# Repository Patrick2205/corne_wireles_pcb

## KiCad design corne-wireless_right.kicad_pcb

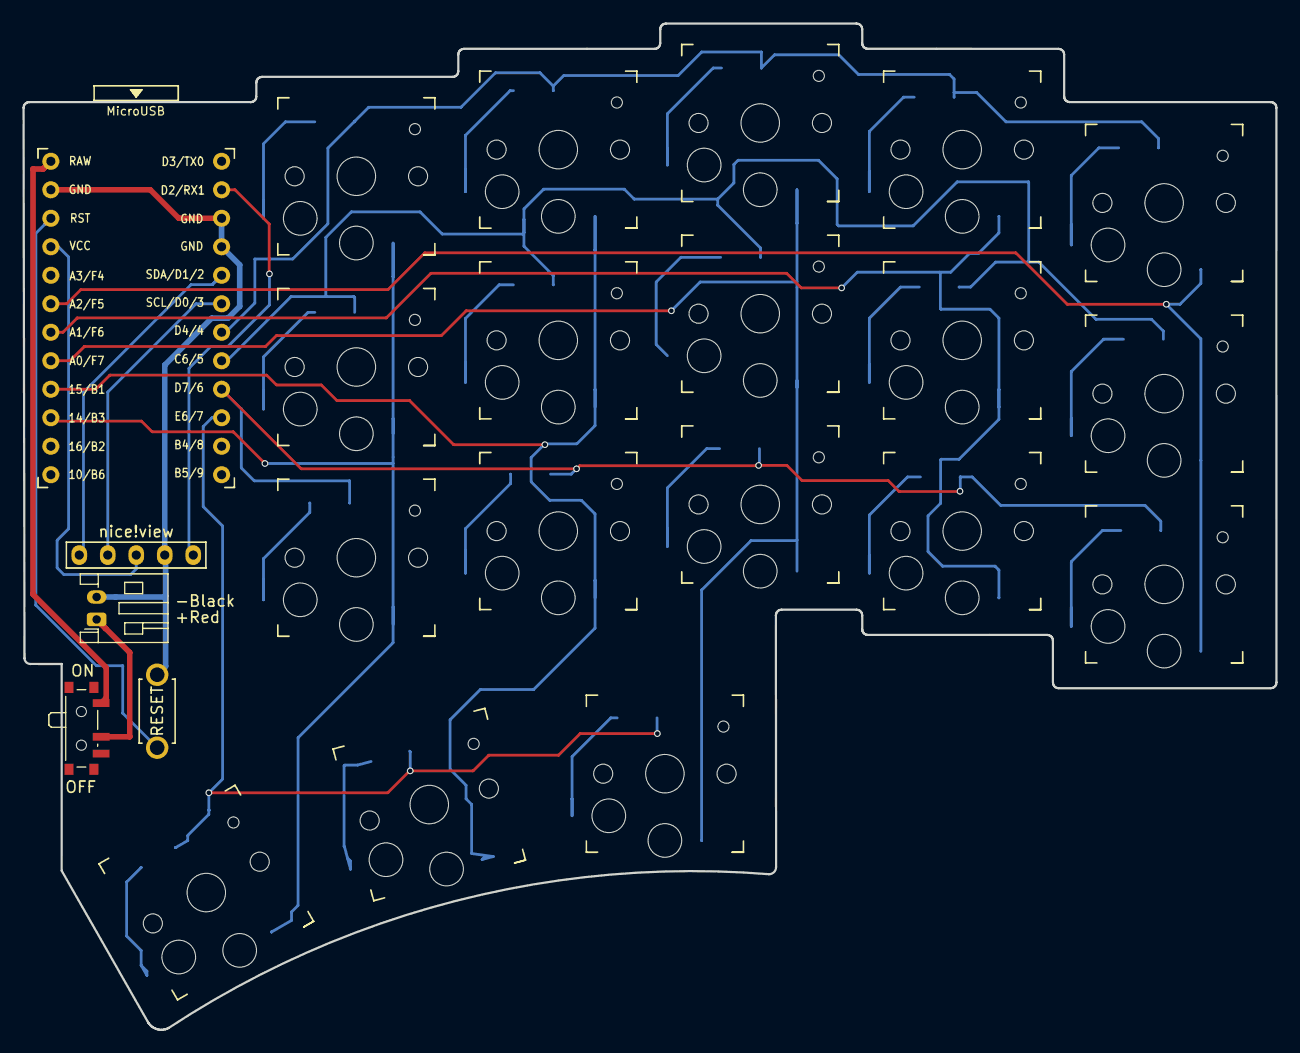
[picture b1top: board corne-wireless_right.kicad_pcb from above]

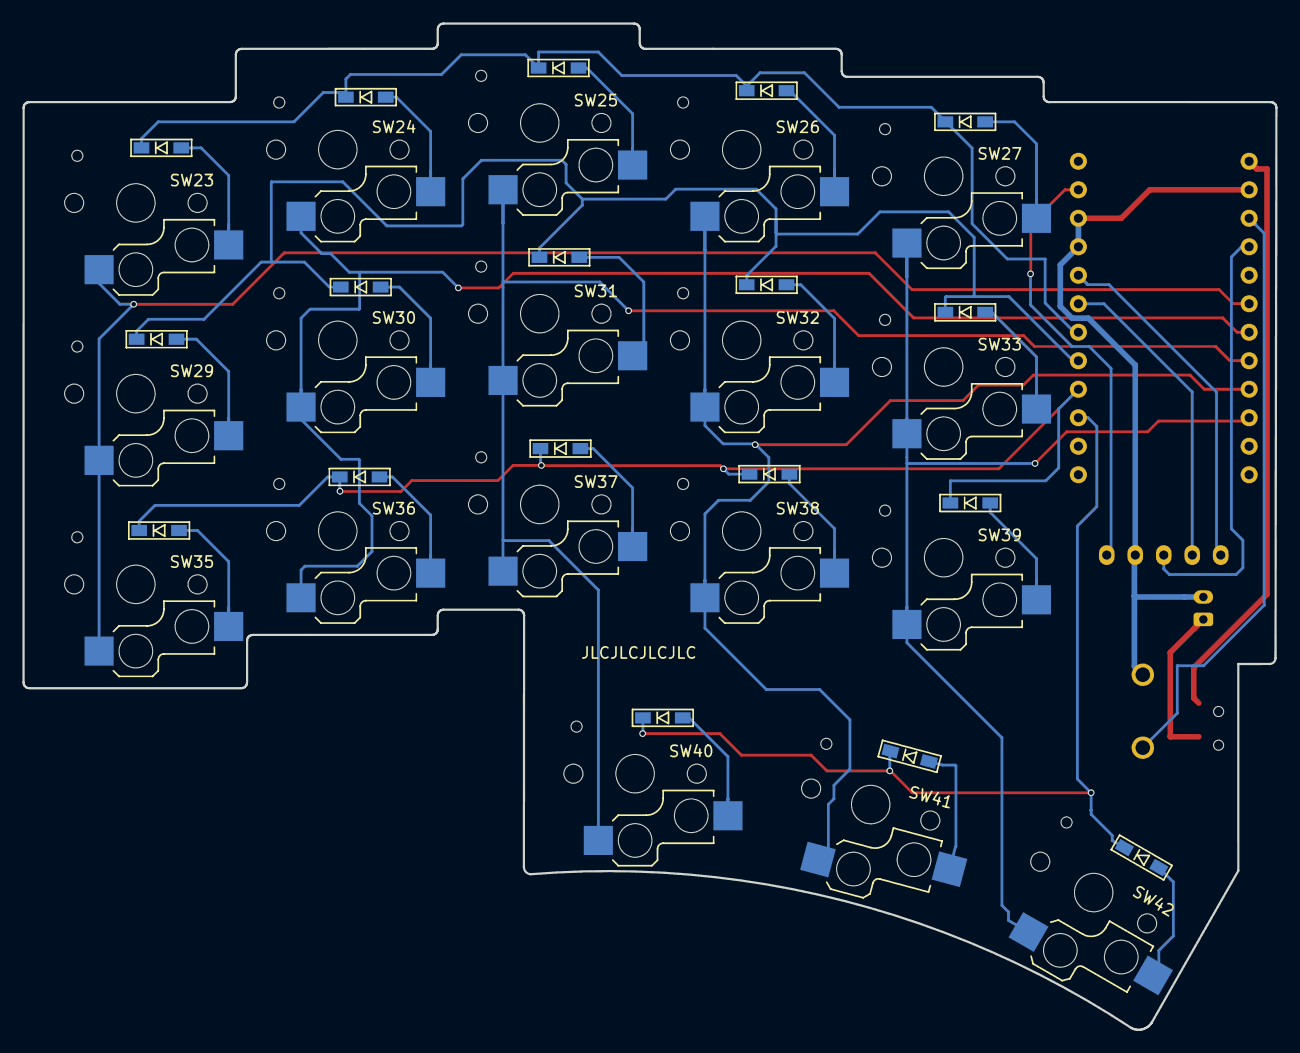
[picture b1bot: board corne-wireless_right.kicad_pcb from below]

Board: 2 copper layers, 111.7 x 89.7 mm, 41 parts (18 on the bottom side), 35 nets.

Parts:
BATJ4: Conn_01x02_Female; JST_PH_S2B-PH-K_1x02_P2.00mm_Horizontal
D23, D24, D25, D26, D27, D29, D30, D31, D32, D33, D35, D36, D37, D38, D39, D40, D41, D42: D; D3_SMD_v2
J7: OLED; nice_view_1side
PSW2: SW_SPST; SW_SPDT_PCM12
RSW2: SW_PUSH; ResetSW_1side
SW23, SW24, SW25, SW26, SW27, SW29, SW30, SW31, SW32, SW33, SW35, SW36, SW37, SW38, SW39, SW40, SW41, SW42: SW_PUSH; Kailh_socket_PG1350_no_LED
U2: ProMicro; ProMicro_v3

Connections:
+BATTA: PSW2.1 (A), U2.24 (RAW)
CS_r: J7.5, U2.2 (RX1/D2)
GNDA: BATJ4.2, J7.4, RSW2.2, U2.3 (GND), U2.4 (GND), U2.23 (GND)
unnamed: BATJ4.1, PSW2.2 (B)
unnamed: D23.2 (A), SW23.2
unnamed: D24.2 (A), SW24.2
unnamed: D25.2 (A), SW25.2
unnamed: D26.2 (A), SW26.2
unnamed: D27.2 (A), SW27.2
unnamed: D29.2 (A), SW29.2
unnamed: D30.2 (A), SW30.2
unnamed: D31.2 (A), SW31.2
unnamed: D32.2 (A), SW32.2
unnamed: D33.2 (A), SW33.2
unnamed: D35.2 (A), SW35.2
unnamed: D36.2 (A), SW36.2
unnamed: D37.2 (A), SW37.2
unnamed: D38.2 (A), SW38.2
unnamed: D39.2 (A), SW39.2
unnamed: D40.2 (A), SW40.2
unnamed: D41.2 (A), SW41.2
unnamed: D42.2 (A), SW42.2
SCL_r: J7.2, U2.6 (3/D0/SCL)
SDA_r: J7.1, U2.5 (2/D1/SDA)
VDD: J7.3, U2.21 (VCC)
col1_r: SW23.1, SW29.1, SW35.1, U2.19 (F5/A2)
col2_r: SW24.1, SW30.1, SW36.1, U2.18 (F6/A1)
col3_r: SW25.1, SW31.1, SW37.1, SW40.1, U2.17 (F7/A0)
col4_r: SW26.1, SW32.1, SW38.1, SW41.1, U2.16 (B1/15)
col5_r: SW27.1, SW33.1, SW39.1, SW42.1, U2.15 (B3/14)
reset_r: RSW2.1, U2.22 (RST)
row0_r: D23.1 (K), D24.1 (K), D25.1 (K), D26.1 (K), D27.1 (K), U2.7 (4/D4)
row1_r: D29.1 (K), D30.1 (K), D31.1 (K), D32.1 (K), D33.1 (K), U2.8 (5/C6)
row2_r: D35.1 (K), D36.1 (K), D37.1 (K), D38.1 (K), D39.1 (K), U2.9 (6/D7)
row3_r: D40.1 (K), D41.1 (K), D42.1 (K), U2.10 (7/E6)

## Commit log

2023-11-02 adding kicad project
